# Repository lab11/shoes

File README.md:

Shoes!
======

BLE + shoelaces

Cloning This Repo
-----------------

When cloning this git repo, be sure to do so with submodules. The software
for this project depends on [nrf5x-base](https://github.com/lab11/nrf5x-base),
and to make sure you have the correct version of that repository, you need
to ensure that the submodule is checked out.

    git clone --recursive https://github.com/lab11/shoes.git

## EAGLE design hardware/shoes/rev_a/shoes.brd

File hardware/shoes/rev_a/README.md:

Shoes HW Rev A
==============

The shoes hardware PCB consists of:
- A Nordic nRF51822
- Two 2 color thru-hole LEDs
- A center push button
- An ADXL362 accelerometer

The nRF51822 BLE radio and processor is programmable over JTAG using the JLink JLinkExe program.
More information about programming the nRF51822 can he found
[here](https://github.com/lab11/nrf5x-base#program-a-nrf51822).

PCB Files
---------

The PCB was designed in [Eagle](http://www.autodesk.com/products/eagle/overview)
(version 6, but it should work in newer versions too.
Also committed are the gerbers that were used to manufacturer the first
revision of the boards.

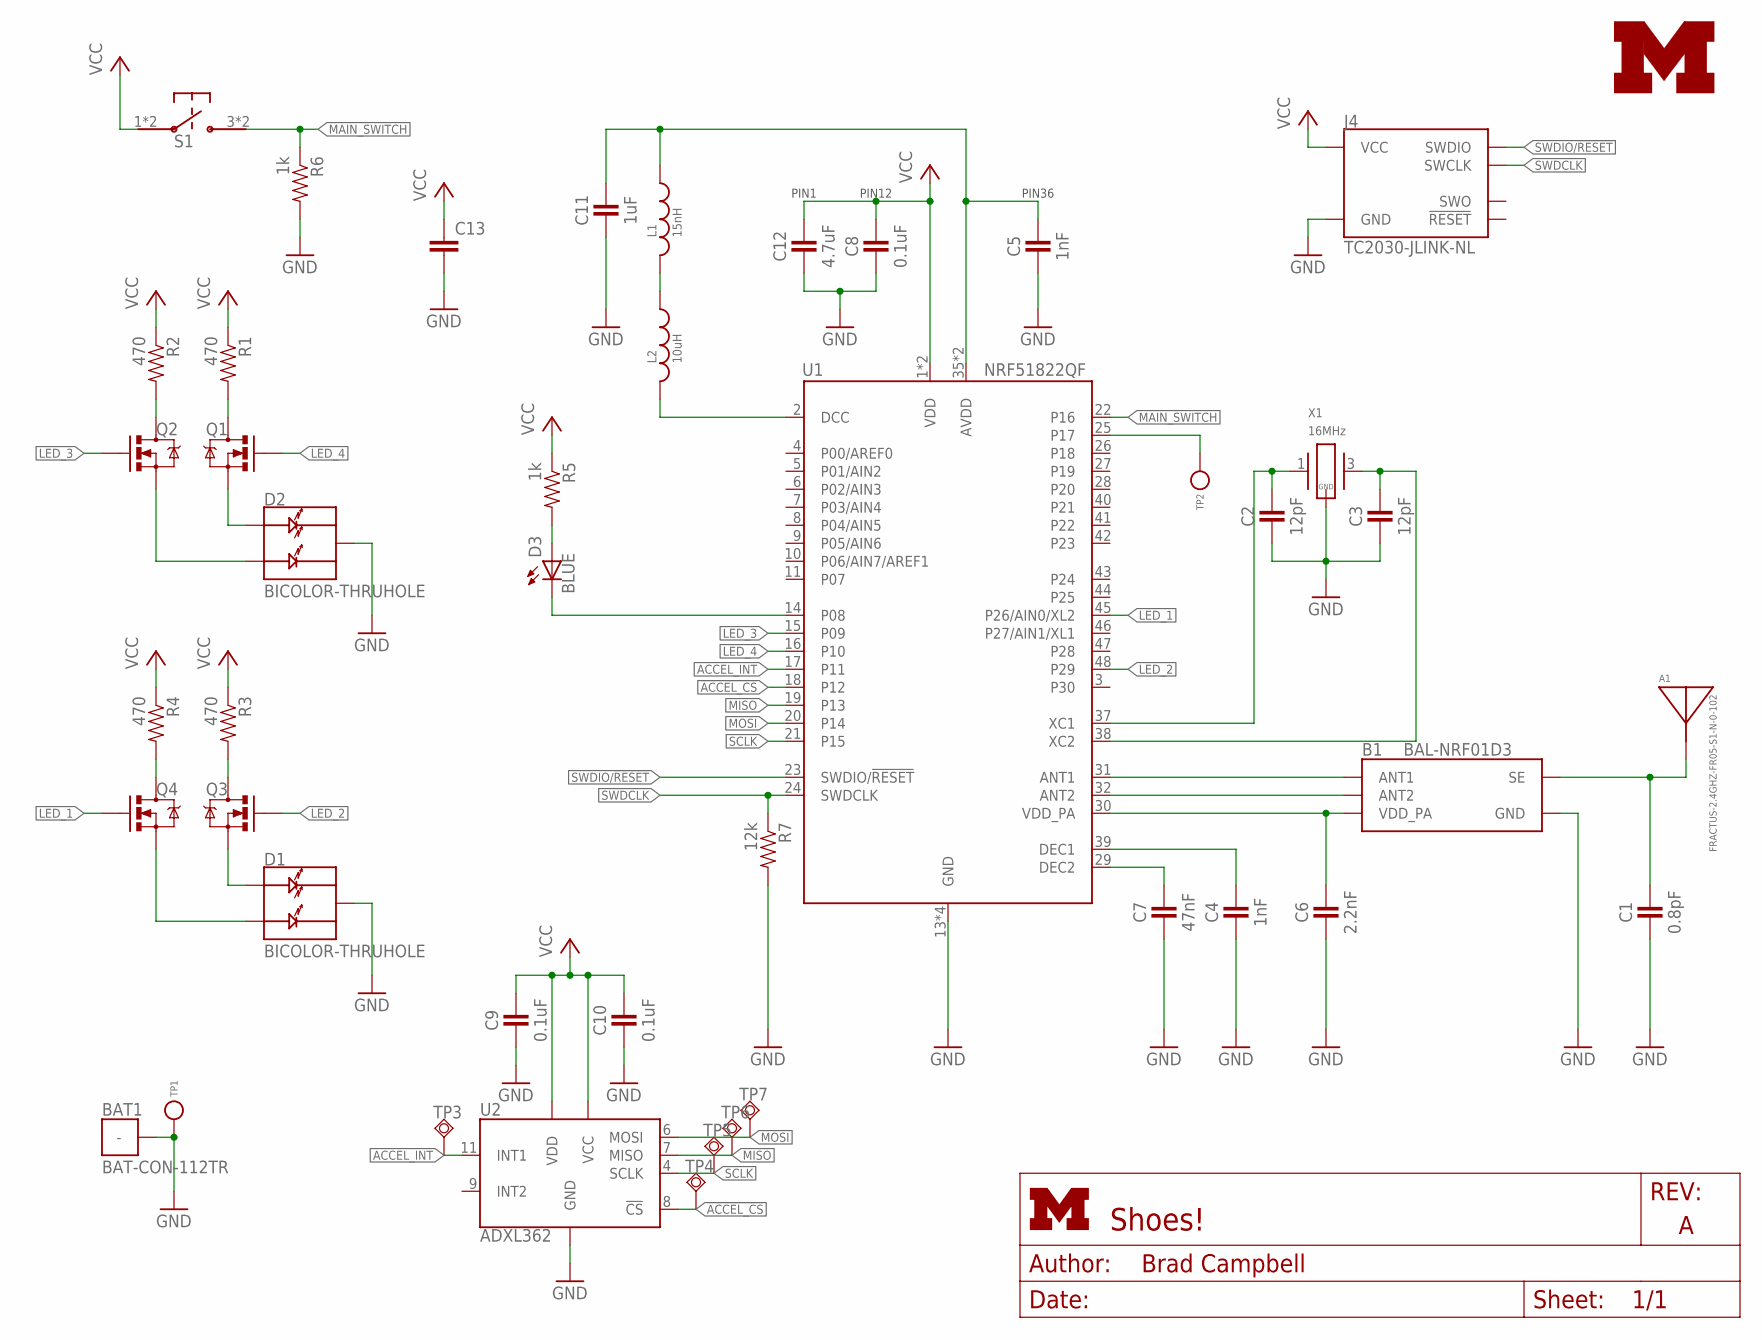
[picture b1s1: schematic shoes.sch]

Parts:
A1: FRACTUS-2.4GHZ-FR05-S1-N-0-102; FRACTUS-ANTENNA-FR05-S1-N-0-102
B1: BAL-NRF01D3
BAT1: BAT-CON-112TR
C1: 0.8pF; 0402_CAP; DIGIKEY 490-6269-1-ND
C2, C3: 12pF; 0402_CAP; DIGIKEY 490-6197-1-ND
C4, C5: 1nF; 0402_CAP; DIGIKEY 490-1303-1-ND
C6: 2.2nF; 0402_CAP; DIGIKEY 490-5419-1-ND
C7: 47nF; 0402_CAP; DIGIKEY 445-1264-1-ND
C8, C9, C10: 0.1uF; 0402_CAP; DIGIKEY 445-4952-1-ND
C11: 1uF; 0402_CAP; DIGIKEY 1276-1513-1-ND
C12: 4.7uF; 0402_CAP; DIGIKEY 445-5947-1-ND
C13: CAP0805; 0805
D1, D2: BICOLOR-THRUHOLE; 3AXIS-0.1IN
D3: BLUE; LED-0603
J4: TC2030-JLINK-NL; TC2030-IDC-NL
L1: 15nH; 0402_CAP; DIGIKEY 587-1521-1-ND
L2: 10uH; 0603_CAP; DIGIKEY 490-4025-1-ND
LOGO3: UMICH_SOLID_TINY; UMICH_SOLID_50MIL
Q1, Q2, Q3, Q4: MOSFET-NCHANNELXFDN-3; XFDFN-3
R1, R2, R3, R4: 470; 0402_RES; DIGIKEY RHM470CDCT-ND
R5, R6: 1k; 0402_RES; DIGIKEY RHM1.0KCECT-ND
R7: 12k; 0402_RES; DIGIKEY RHM12.0KCDCT-ND
S1: TL3315NF100Q
TP1, TP2: TEST_POINT_0.020IN; TESTPOINT_0.020IN
TP3, TP4, TP5, TP6, TP7: TPSQTP06SQ; TP06SQ
U1: NRF51822QF; QFN-48-6MM
U2: ADXL362; TFLGA-16/3.3MMX3.1MM
X1: 16MHz; TXC-8Y; DIGIKEY 887-2003-1-ND

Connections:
!ACCEL_CS: TP4.TP, U1.18 (P12), U2.8 (!CS)
ACCEL_INT: TP3.TP, U1.17 (P11), U2.11 (INT1)
AVDD: C5.1, C11.1, L1.1, U1.35 (AVDD), U1.36 (AVDD)
DCC: L2.2, U1.2 (DCC)
GND: B1.GND, BAT1.PAD, C1.2, C2.2, C3.2, C4.2, C5.2, C6.2, C7.2, C8.2, C9.2, C10.2, C11.2, C12.2, C13.2, D1.M (C), D2.M (C), J4.5 (GND), R6.2, R7.2, TP1.TESTPOINT, U1.13 (GND), U1.33 (GND), U1.34 (GND), U1.GND, U2.12 (GND), U2.13 (GND), U2.16 (GND), X1.2 (GND), X1.4 (GND)
LED_1: Q4.G, U1.45 (P26/AIN0/XL2)
LED_2: Q3.G, U1.48 (P29)
LED_3: Q2.G, U1.15 (P09)
LED_4: Q1.G, U1.16 (P10)
MAIN_SWITCH: R6.1, S1.3, S1.4, U1.22 (P16)
MISO: TP6.TP, U1.19 (P13), U2.7 (MISO)
MOSI: TP7.TP, U1.20 (P14), U2.6 (MOSI)
unnamed: TP2.TESTPOINT, U1.25 (P17)
unnamed: D2.1 (A1), Q1.S
unnamed: B1.ANT1, U1.31 (ANT1)
unnamed: B1.ANT2, U1.32 (ANT2)
unnamed: D3.C, U1.14 (P08)
unnamed: D2.2 (A2), Q2.S
unnamed: Q2.D, R2.2
unnamed: Q1.D, R1.2
unnamed: A1.1, B1.SE, C1.1
unnamed: D1.1 (A1), Q3.S
unnamed: D1.2 (A2), Q4.S
unnamed: L1.2, L2.1
unnamed: Q4.D, R4.2
unnamed: C2.1, U1.37 (XC1), X1.1
unnamed: C3.1, U1.38 (XC2), X1.3 (2)
unnamed: C4.1, U1.39 (DEC1)
unnamed: C7.1, U1.29 (DEC2)
unnamed: Q3.D, R3.2
unnamed: D3.A, R5.2
SCLK: TP5.TP, U1.21 (P15), U2.4 (SCLK)
SWDCLK: J4.4 (SWCLK), R7.1, U1.24 (SWDCLK)
SWDIO/!RESET: J4.2 (SWDIO), U1.23 (SWDIO/!RESET)
VCC: C8.1, C9.1, C10.1, C12.1, C13.1, J4.1 (VCC), R1.1, R2.1, R3.1, R4.1, R5.1, S1.1, S1.2, U1.1 (VDD), U1.12 (VDD), U2.1 (VDD), U2.14 (VCC)
VDD_PA: B1.VCC (VDD_PA), C6.1, U1.30 (VDD_PA)

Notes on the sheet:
PIN12
PIN1
PIN36

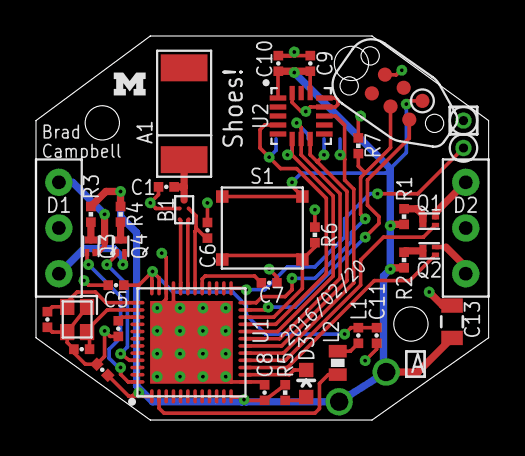
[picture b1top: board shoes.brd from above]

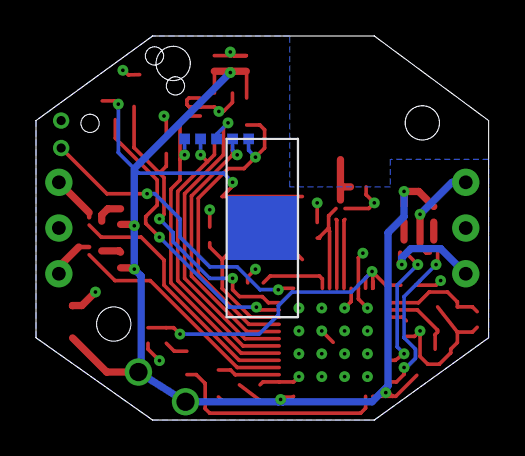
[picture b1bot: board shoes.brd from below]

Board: 2 copper layers, 25.1 x 21.3 mm, 45 parts (6 on the bottom side), 36 nets.

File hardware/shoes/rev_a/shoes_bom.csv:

Qty,Value,Device,Package,Parts,Description,DIGIKEY,MOUSER,NEWARK,RICHARDSON_RFPD
1,FRACTUS-2.4GHZ-FR05-S1-N-0-102,FRACTUS-2.4GHZ-FR05-S1-N-0-102,FRACTUS-ANTENNA-FR05-S1-N-0-102,A1,"Fractus Compact Reach XtendTM chip antenna is engineered specifically for Bluetooth,",,,,FR05-S1-N-0102B
1,BAL-NRF01D3,BAL-NRF01D3,BAL-NRF01D3,B1,"50 ohm nominal input / conjugate match balun to nRF51422-QFAA,",497-13637-1-ND,511-BAL-NRF01D3,,
1,0.8pF,CAPACITOR,0402_CAP,C1,0402 Capacitor,490-6269-1-ND,,,
2,12pF,CAPACITOR,0402_CAP,"C2, C3",0402 Capacitor,490-6197-1-ND,,,
2,1nF,CAPACITOR,0402_CAP,"C4, C5",0402 Capacitor,490-1303-1-ND,,,
1,2.2nF,CAPACITOR,0402_CAP,C6,0402 Capacitor,490-5419-1-ND,,,
1,47nF,CAPACITOR,0402_CAP,C7,0402 Capacitor,445-1264-1-ND,,,
3,0.1uF,CAPACITOR,0402_CAP,"C8, C9, C10",0402 Capacitor,445-4952-1-ND,,,
1,1uF,CAPACITOR,0402_CAP,C11,0402 Capacitor,1276-1513-1-ND,,,
1,4.7uF,CAPACITOR,0402_CAP,C12,0402 Capacitor,445-5947-1-ND,,,
2,BICOLOR-THRUHOLE,BICOLOR-THRUHOLE,3AXIS-0.1IN,"D1, D2",3 axis thru-hold LED,,,,
1,BLUE,LED0603,LED-0603,D3,LEDs,,,,
1,15nH,INDUCTOR0402,0402_CAP,L1,,587-1521-1-ND,,,
1,10uH,INDUCTOR0603,0603_CAP,L2,,490-4025-1-ND,,,
4,MOSFET-NCHANNELXFDN-3,MOSFET-NCHANNELXFDN-3,XFDFN-3,"Q1, Q2, Q3, Q4",Generic NMOS footprint,DMN2400UFB4-7DICT-ND,,,
4,470,RESISTOR,0402_RES,"R1, R2, R3, R4",Resistor,RHM470CDCT-ND,,,
2,1k,RESISTOR,0402_RES,"R5, R6",Resistor,RHM1.0KCECT-ND,,,
1,12k,RESISTOR,0402_RES,R7,Resistor,RHM12.0KCDCT-ND,,,
1,TL3315NF100Q,TL3315NF100Q,TL3315NF100Q,S1,SWITCH TACTILE SPST-NO 0.05A 15V,EG4620CT-ND,,,
1,NRF51822QF,NRF51822QF,QFN-48-6MM,U1,Multiprotocol Bluetooth® 4.0 low energy/2.4 GHz RF SoC,1490-1042-1-ND,949-NRF51822-QFAC-R7,,
1,ADXL362,ADXL362,TFLGA-16/3.3MMX3.1MM,U2,IC ACCEL DIG LO PWR 3AX 16LGA,ADXL362BCCZ-RL7CT-ND,584-ADXL362BCCZ-R7,47W0478,
1,16MHz,TXC-8Y,TXC-8Y,X1,2mmx1.6mm SMD Crystal,887-2003-1-ND,,,

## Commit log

2016-02-20 first pass on PCB
2016-02-20 readme
2016-02-21 start on app
2016-02-21 the other nodes toggle when one node moves
2016-02-21 enable dc dc seems to help
2016-02-21 board changes
    added cap from power to ground
2016-02-21 move antenna back
2016-02-23 add shoes simulation
2016-02-23 change to fabric
2016-02-23 update simulation, not sure how useful
2016-02-23 update pcb
2016-02-23 add gitignorest pu
2016-02-23 advertise on 1 channel
2016-02-23 new app for shoes
    uses timeslot/raw radio access
2016-02-24 working pared down listener
2016-02-24 update raw app
2016-02-24 clean up app a bit
2016-02-24 add files about pcb
2016-03-02 new PCB preliminary working
2016-03-02 button works, lace LEDs work
2016-03-05 add pic
2016-03-05 add pic to readme
2016-03-09 better toggle?
2016-03-10 many updates to app
2016-03-13 updated to sdk 11.0.0
    also cleaned up code
2016-03-13 check that we don't get our own flood
2016-03-13 add costs to bom
2016-04-24 got DFU working
2016-05-10 added button press state machine
2016-05-10 enable restarting
2016-05-10 checkpoint
2016-05-10 little cleanup
2016-05-11 not totally broken
2016-05-11 delayed led
2016-05-11 extended packet
2016-05-11 one hop flood sync
2016-05-11 multi hop working again i think
2016-05-12 best version so far
2016-05-12 update nrf5x-base
2016-05-13 working
2016-05-13 fix TX range issue
2016-05-13 clean up shoes-raw
2016-05-13 rename shoes-raw to just shoes
2016-05-13 longer stay on period
2017-03-27 add readme
2017-03-27 add note about submodules
2017-03-27 software info

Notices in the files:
parts and their libraries:
SparkFun-LED: Licensing: CC v3.0 Share-Alike You are welcome to use this library for commercial purposes.
